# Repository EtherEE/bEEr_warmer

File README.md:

# bEEr_warmer
A simple PCB as a beer mug warmer powered by The USB type C Power Delivery source

## Table of contents
* [General info](#general-info)
* [Topology](#topology)
* [PCB](#pcb)
* [Setup](#setup)
* [Status](#status)
* [License](#license)
## General info
Gadget built for my colleague - PCB board as a heat keeper for hot drinks like mulled wine, beer or regular tea.
The board requires electronic configuration (selection of resistors) and uploading software to the microcontroller.
## Topology

## PCB
The PCB was designed in current KiCad version. All necessary files are in the documentation folder.
## Setup
The gadget uses the AP33771 chip as a Pawer Delivery sink. The output voltage and delivered power is configured using resistors. For the resistor values shown in the schematic, the controller delivers 9V at a maximum power of 20W. Such settings worked well in my implementation of the board. With no load in the form of a mug of beer, the board heats up to 70 degrees in 30 seconds. Keep in mind that my PD sink circuit configuration depends on the resistance of the load. In the JLCPCB board design, the load resistance was about 4.3 Ohms at an ambient temperature of 21 degrees, and was in accordance with the calculations of the Saturn PCB Design calculator. If the load resistance of the manufactured boards will differ from the intended one, the voltage and power settings provided by the PD source should be adjusted accordingly. On the first page of the schematic diagram there are two tables from which you can read the desired values of the voltage and power configuration resistors. For 9V, R28 and R29 must not be soldered in. To get 20W R30 must be 26k Ohm. After checking the value of the load resistance and selecting the appropriate PD sink configuration resistors, the two solder bridges (JP1 and JP2) should be soldered together. This will lead the current to the load. Two additional resistors should not be soldered on the PCB: R13 and R32.

To program the STM32 microcontroller, use the ST Link programmer, the SWDIO and SWCLK pins are brought out on the popular DF13A socket. The program is trivial and its listing can be found in the documentation folder. Digital and one analog outputs from all temperature sensors and a proximity sensor have been fed to the microcontroller. The microcontroller has a large percentage of unused memory resources. There is a huge room for maneuver and for expanding the functionality of the software. By changing the software, the number of temperature sensors can be reduced, thus reducing the cost of the board.

The AND gate is used to protect the circuit from overheating and against software or microcontroller errors. When any of the inputs is low, the current from the load is disconnected. The inputs of the gate are:
- 85 degree sensor output
- touch sensor output
- output from the microcontroller

Two LEDs are used to monitor the status of the device:
- LED_TEST. Is used to control LED flickering. The user is notified of the system status from the LED flashing pattern. Any non-PD power source is not supported in the AP33771, and the LED will show the mismatch accordingly.

- LED. It is controlled by a microcontroller. Flashing at a frequency of once per second means that current is being applied to the load. If the diode shines continuously, the device has reached a temperature of about 70 degrees. If the diode flashes quickly (about 2 times per second) there is an error in reading the temperature sensor.

After checking the fucnition of the board, I suggest you desolder the DF13A socket and put conformal coating on both sides of the board to protect the circuit from possible damage from flooding.
## Status
Task closed
## License
MIT

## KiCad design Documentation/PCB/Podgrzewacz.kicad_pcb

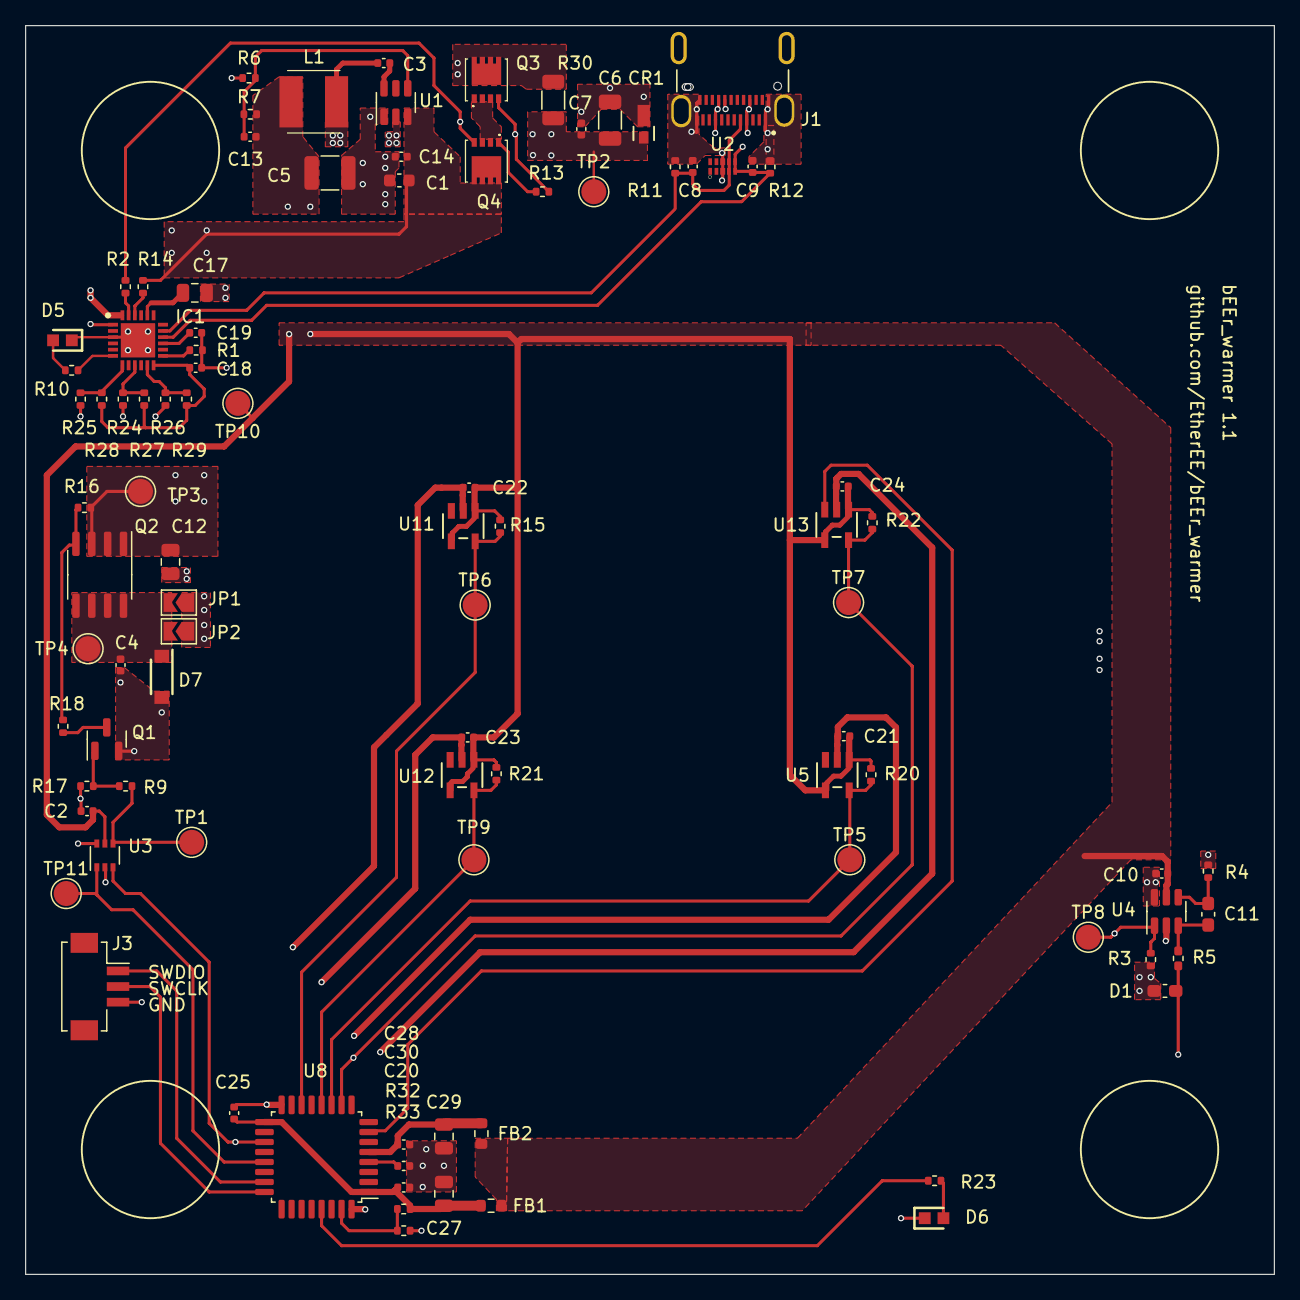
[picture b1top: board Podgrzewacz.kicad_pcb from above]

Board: 4 copper layers, 100.0 x 100.0 mm, 94 parts (0 on the bottom side), 46 nets.

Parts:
C1: 1u; C_0603_1608Metric
C2, C3, C4, C7, C10, C14, C18, C19, C20, C21, C22, C23, C24, C25, C30: 100n; C_0402_1005Metric
C5: 47u; C_1210_3225Metric
C6: 10u; C_1206_3216Metric
C8, C9: 27p; C_0402_1005Metric
C11: 2n2-47n; C_0603_1608Metric_Pad1.08x0.95mm_HandSolder
C12, C17, C29: 1u; C_0805_2012Metric
C13: 56p; C_0402_1005Metric
C27: 4,7u; C_0805_2012Metric
C28: 10n; C_0402_1005Metric
CR1: MSMP20A-M3/89A; CR_0A-M3&slash_89A_VIS
D1: TESDU5V0 RGG; C_0603_1608Metric_Pad1.08x0.95mm_HandSolder
D5, D6: 150060AS75000; LEDC1608X80N
D7: NRVS1MFL; SODFL3617X108N
FB1, FB2: BLM18EG221SN1D; R_0603_1608Metric
IC1: AP33771DKZ-13; QFN50P400X400X80-25N-D
J1: CX90B1-24P; HRS_CX90B1-24P
J3: DF13A-3P-1.25H_51_; Hirose_DF13C_CL535-0403-5-51_1x03-1MP_P1.25mm_Vertical
JP1, JP2: SolderJumper_2_Bridged; SolderJumper-2_P1.3mm_Open_TrianglePad1.0x1.5mm
L1: 15uH; LQH5BPB100MT0L
Q1: MMFTN3402; SOT-23
Q2: AO4447A; SOIC-8_3.9x4.9mm_P1.27mm
Q3, Q4: DMN3008SFGQ-7; DMG7401SFG13
R1: 56k; R_0402_1005Metric
R2: 100R; R_0402_1005Metric
R3, R7, R13, R16, R17, R24, R25, R26, R32: 100k; R_0402_1005Metric
R4: 1M; R_0402_1005Metric
R5: 4k7-33k; R_0402_1005Metric_Pad0.72x0.64mm_HandSolder
R6: 22k1; R_0402_1005Metric
R9, R10, R23: 1k; R_0402_1005Metric
R11, R12: 5k1; R_0402_1005Metric
R14, R27, R28, R29, R33: 0R; R_0402_1005Metric
R15, R20, R21, R22: 22k; R_0402_1005Metric
R18: 10k; R_0402_1005Metric
R30: 10mR; R_1206_3216Metric
TP1, TP2, TP3, TP4, TP5, TP6, TP7, TP8, TP9, TP10, TP11: TestPoint; TestPoint_Pad_D2.0mm
U1: TPS54202DDCR; SOT-23-6
U2: TPD4E02B04DQA; DQA_R-PUSON-N10_
U3: 74LVC1G11DW-7; SOT-363_SC-70-6
U4: AT42QT1012-T; SOT-23-6
U5, U12: LM26CIM5-SPA/NOPB; MF05A
U8: STM32F030K6Tx; LQFP-32_7x7mm_P0.8mm
U11: LM26CIM5-RPA/NOPB; MF05A
U13: LM26CIM5-TPA/NOPB; MF05A

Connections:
65DEG: R15.1, TP6.1, U8.14 (PB0), U11.5 (OS/~OS)
75DEG_A: R21.1, TP9.1, U8.12 (PA6), U12.5 (OS/~OS)
75DEG_B: R20.1, TP5.1, U5.5 (OS/~OS), U8.11 (PA5)
85DEG: R22.1, TP7.1, U3.6, U8.10 (PA4), U13.5 (OS/~OS)
+3.3V: C2.2, C5.1, C10.2, C13.1, C21.1, C22.1, C23.1, C24.1, FB1.1, FB2.2, L1.2, R7.2, R15.2, R20.2, R21.2, R22.2, TP10.1, U3.5 (VCC), U4.5 (VDD), U5.1 (HYST), U5.4 (V+), U11.1 (HYST), U11.4 (V+), U12.1 (HYST), U12.4 (V+), U13.1 (HYST), U13.4 (V+)
CC1: C8.1, IC1.17 (CC1), J1.A5 (CC1), R11.2, U2.4 (IO3), U2.7 (NC)
CC2: C9.1, IC1.16 (CC2), J1.B5 (CC2), R12.2, U2.5 (IO4), U2.6 (NC)
Control: TP11.1, U3.1, U8.21 (PA11)
GND: C1.2, C2.1, C4.2, C5.2, C6.2, C7.2, C8.2, C9.2, C10.1, C12.2, C14.2, C17.2, C18.2, C19.2, C20.1, C21.2, C22.2, C23.2, C24.2, C25.1, C27.2, C28.1, C29.1, C30.1, CR1.2, D1.1 (A1), D5.1 (K), D6.1 (K), D7.2, IC1.3 (GND), IC1.25 (EP), J1.A1 (GND_1A), J1.A12 (GND_2A), J1.B1 (GND_1B), J1.B12 (GND_2B), J1.P1 (SHIELD), J1.P2 (SHIELD), J1.P3 (SHIELD), J1.P4 (SHIELD), J3.3, JP1.1 (A), JP2.1 (A), Q1.2 (S), R1.2, R3.2, R4.2, R6.1, R11.1, R12.1, R17.2, R24.2, R25.2, R26.2, R33.1, U1.1 (GND), U2.3 (G), U2.8 (G), U3.2 (GND), U4.2 (VSS), U4.6 (TIME), U5.2 (GND), U8.16 (VSS), U8.32 (VSS), U11.2 (GND), U12.2 (GND), U13.2 (GND)
LED: R23.2, U8.29 (PB6)
LED_TEST: IC1.6 (GPIO4), R10.2
LOAD: C4.1, D7.1, JP1.2 (B), JP2.2 (B), Q2.5 (D), Q2.6 (D), Q2.7 (D), Q2.8 (D), TP4.1
unnamed: C20.2, C25.2, C27.1, FB1.2, R32.2, U8.1 (VDD), U8.17 (VDD)
unnamed: D5.2 (A), R10.1
unnamed: D6.2 (A), R23.1
unnamed: C19.1, IC1.15 (IFB)
unnamed: IC1.13 (PSEL), R1.1
unnamed: IC1.23 (PWR_EN), R2.2
unnamed: C17.1, IC1.20 (V5V)
unnamed: IC1.22 (VBUS), R14.2
unnamed: IC1.24 (VCC), Q3.5 (D_1), Q3.6 (D_2), Q3.7 (D_3), Q3.8 (D_4), R30.2
unnamed: Q1.3 (D), R18.2
unnamed: Q1.1 (G), R9.2, R17.1
unnamed: Q2.4 (G), R16.2, R18.1
unnamed: Q3.4 (G), Q4.4 (G), R2.1, R13.2
unnamed: Q3.1 (S_1), Q3.2 (S_2), Q3.3 (S_3), Q4.1 (S_1), Q4.2 (S_2), Q4.3 (S_3), R13.1
unnamed: R9.1, TP1.1, U3.4
unnamed: C3.2, U1.6 (BOOT)
unnamed: C13.2, R6.2, R7.1, U1.4 (FB)
unnamed: C3.1, L1.1, U1.2 (SW)
unnamed: C11.2, R4.1, U4.4 (SNS)
unnamed: C11.1, R5.1, U4.3 (SNSK)
unnamed: R32.1, R33.2, U8.31 (BOOT0)
unnamed: C30.2, U8.4 (NRST)
unnamed: C28.2, C29.2, FB2.1, U8.5 (VDDA)
SWCLK: J3.2, U8.24 (PA14)
SWDIO: J3.1, U8.23 (PA13)
SensorIN: D1.2 (A2), R5.2
SensorOUT: R3.1, TP8.1, U3.3, U4.1 (OUT), U8.19 (PA9)
Temp: U8.7 (PA1), U13.3 (VTEMP)
V3VD: C18.1, IC1.12 (V3VD), R27.1, R28.1, R29.1
VOUT: C1.1, C12.1, C14.1, Q2.1 (S), Q2.2 (S), Q2.3 (S), Q4.5 (D_1), Q4.6 (D_2), Q4.7 (D_3), Q4.8 (D_4), R14.1, R16.1, TP3.1, U1.3 (VIN)
VSEL0: IC1.9 (VSEL0), R24.1, R27.2
VSEL1: IC1.7 (VSEL1), R25.1, R28.2
VSEL2: IC1.11 (VSEL2), R26.1, R29.2
Vbus: C6.1, C7.1, CR1.1, IC1.1 (ISENP), J1.A4 (VBUS_1A), J1.A9 (VBUS_2A), J1.B4 (VBUS_1B), J1.B9 (VBUS_2B), R30.1, TP2.1

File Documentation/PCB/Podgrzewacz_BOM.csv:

"Id";"Designator";"Footprint";"Quantity";"Designation";"Supplier and ref";
1;"C8,C9";"C_0402_1005Metric";2;"27p";;;
2;"TP11,TP5,TP9,TP7,TP8,TP10,TP6,TP4,TP2,TP1,TP3";"TestPoint_Pad_D2.0mm";11;"TestPoint";;;
3;"U8";"LQFP-32_7x7mm_P0.8mm";1;"STM32F030K6Tx";;;
4;"R33,R14,R27";"R_0402_1005Metric";3;"0R";;;
5;"R6";"R_0402_1005Metric";1;"22k1";;;
6;"C11";"C_0603_1608Metric_Pad1.08x0.95mm_HandSolder";1;"2n2-47n";;;
7;"C28";"C_0402_1005Metric";1;"10n";;;
8;"R10,R9,R23";"R_0402_1005Metric";3;"1k";;;
9;"R11,R12";"R_0402_1005Metric";2;"5k1";;;
10;"CR1";"CR_0A-M3&slash_89A_VIS";1;"MSMP20A-M3/89A";;;
11;"U4";"SOT-23-6";1;"AT42QT1012-T";;;
12;"C13";"C_0402_1005Metric";1;"56p";;;
13;"C10,C4,C24,C19,C25,C14,C7,C18,C22,C2,C21,C3,C23,C30,C20";"C_0402_1005Metric";15;"100n";;;
14;"R3,R7,R25,R24,R16,R26,R17";"R_0402_1005Metric";7;"100k";;;
15;"Q3,Q4";"DMG7401SFG13";2;"DMN3008SFGQ-7";;;
16;"J3";"Hirose_DF13C_CL535-0403-5-51_1x03-1MP_P1.25mm_Vertical";1;"DF13A-3P-1.25H_51_";;;
17;"U13";"MF05A";1;"LM26CIM5-TPA/NOPB";;;
18;"U12,U5";"MF05A";2;"LM26CIM5-SPA/NOPB";;;
19;"C27";"C_0805_2012Metric";1;"4,7u";;;
20;"FB2,FB1";"R_0603_1608Metric";2;"BLM18EG221SN1D";;;
21;"D5,D6";"LEDC1608X80N";2;"150060AS75000";;;
22;"C6";"C_1206_3216Metric";1;"10u";;;
23;"R18";"R_0402_1005Metric";1;"10k";;;
24;"U11";"MF05A";1;"LM26CIM5-RPA/NOPB";;;
25;"R1";"R_0402_1005Metric";1;"56k";;;
26;"D1";"C_0603_1608Metric_Pad1.08x0.95mm_HandSolder";1;"TESDU5V0 RGG";;;
27;"U3";"SOT-363_SC-70-6";1;"74LVC1G11DW-7";;;
28;"C29,C12,C17";"C_0805_2012Metric";3;"1u";;;
29;"U2";"DQA_R-PUSON-N10_";1;"TPD4E02B04DQA";;;
30;"Q2";"SOIC-8_3.9x4.9mm_P1.27mm";1;"AO4447A";;;
31;"C1";"C_0603_1608Metric";1;"1u";;;
32;"C5";"C_1210_3225Metric";1;"47u";;;
33;"Q1";"SOT-23";1;"MMFTN3402";;;
34;"R21,R15,R20,R22";"R_0402_1005Metric";4;"22k";;;
35;"R4";"R_0402_1005Metric";1;"1M";;;
36;"J1";"HRS_CX90B1-24P";1;"CX90B1-24P";;;
37;"L1";"LQH5BPB100MT0L";1;"15uH";;;
38;"JP1,JP2";"SolderJumper-2_P1.3mm_Open_TrianglePad1.0x1.5mm";2;"SolderJumper_2_Bridged";;;
39;"R30";"R_1206_3216Metric";1;"10mR";;;
40;"U1";"SOT-23-6";1;"TPS54202DDCR";;;
41;"R2";"R_0402_1005Metric";1;"100R";;;
42;"R5";"R_0402_1005Metric_Pad0.72x0.64mm_HandSolder";1;"4k7-33k";;;
43;"IC1";"QFN50P400X400X80-25N-D";1;"AP33771DKZ-13";;;
44;"D7";"SODFL3617X108N";1;"NRVS1MFL";;;

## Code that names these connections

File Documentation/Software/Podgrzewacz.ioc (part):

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Mcu.Name=STM32F030K6Tx
Mcu.Package=LQFP32
Mcu.UserName=STM32F030K6Tx
PA1.GPIOParameters=GPIO_Label
PA1.GPIO_Label=Temp
PA1.Mode=IN1
PA1.Signal=ADC_IN1
PA11.GPIOParameters=GPIO_Label
PA11.GPIO_Label=Control
PA11.Signal=GPIO_Output
PA13.Mode=Serial_Wire
PA13.Signal=SYS_SWDIO
PA14.Mode=Serial_Wire
PA14.Signal=SYS_SWCLK
PA4.GPIOParameters=GPIO_Label
PA4.GPIO_Label=_85DEG
PA4.Signal=GPIO_Input
PA5.GPIOParameters=GPIO_Label
PA5.GPIO_Label=_75DEG_B
PA5.Signal=GPIO_Input
PA6.GPIOParameters=GPIO_Label
PA6.GPIO_Label=_75DEG_A
PA6.Signal=GPIO_Input
PA9.GPIOParameters=GPIO_Label
PA9.GPIO_Label=SensorOUT
PA9.Signal=GPIO_Input
PB0.GPIOParameters=GPIO_Label
PB0.GPIO_Label=_65DEG
PB0.Signal=GPIO_Input
PB6.GPIOParameters=GPIO_Label
PB6.GPIO_Label=LED
PB6.Signal=GPIO_Output
board=custom

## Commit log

2024-03-11 Create Diagram
2024-03-11 Dodano Diagram.drawio.svg
2024-06-02 Dodano Diagram.svg
2024-06-02 Create PCB
2024-06-02 Create aaa
2024-06-02 Rename REDME.md to README.md
